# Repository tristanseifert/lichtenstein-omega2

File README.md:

# Lichtenstein Omega2+
This is a version of the Lichtenstein hardware, using an [Onion Omega2+](https://onion.io/omega2/) and a MAX V CPLD to drive up to eight LED strips at once.

Connectivity is provided by the Omega2's Ethernet peripheral. The board itself runs a custom version of LEDE, with the lichtenstein client app running and providing lichtenstein services on the local subnet.

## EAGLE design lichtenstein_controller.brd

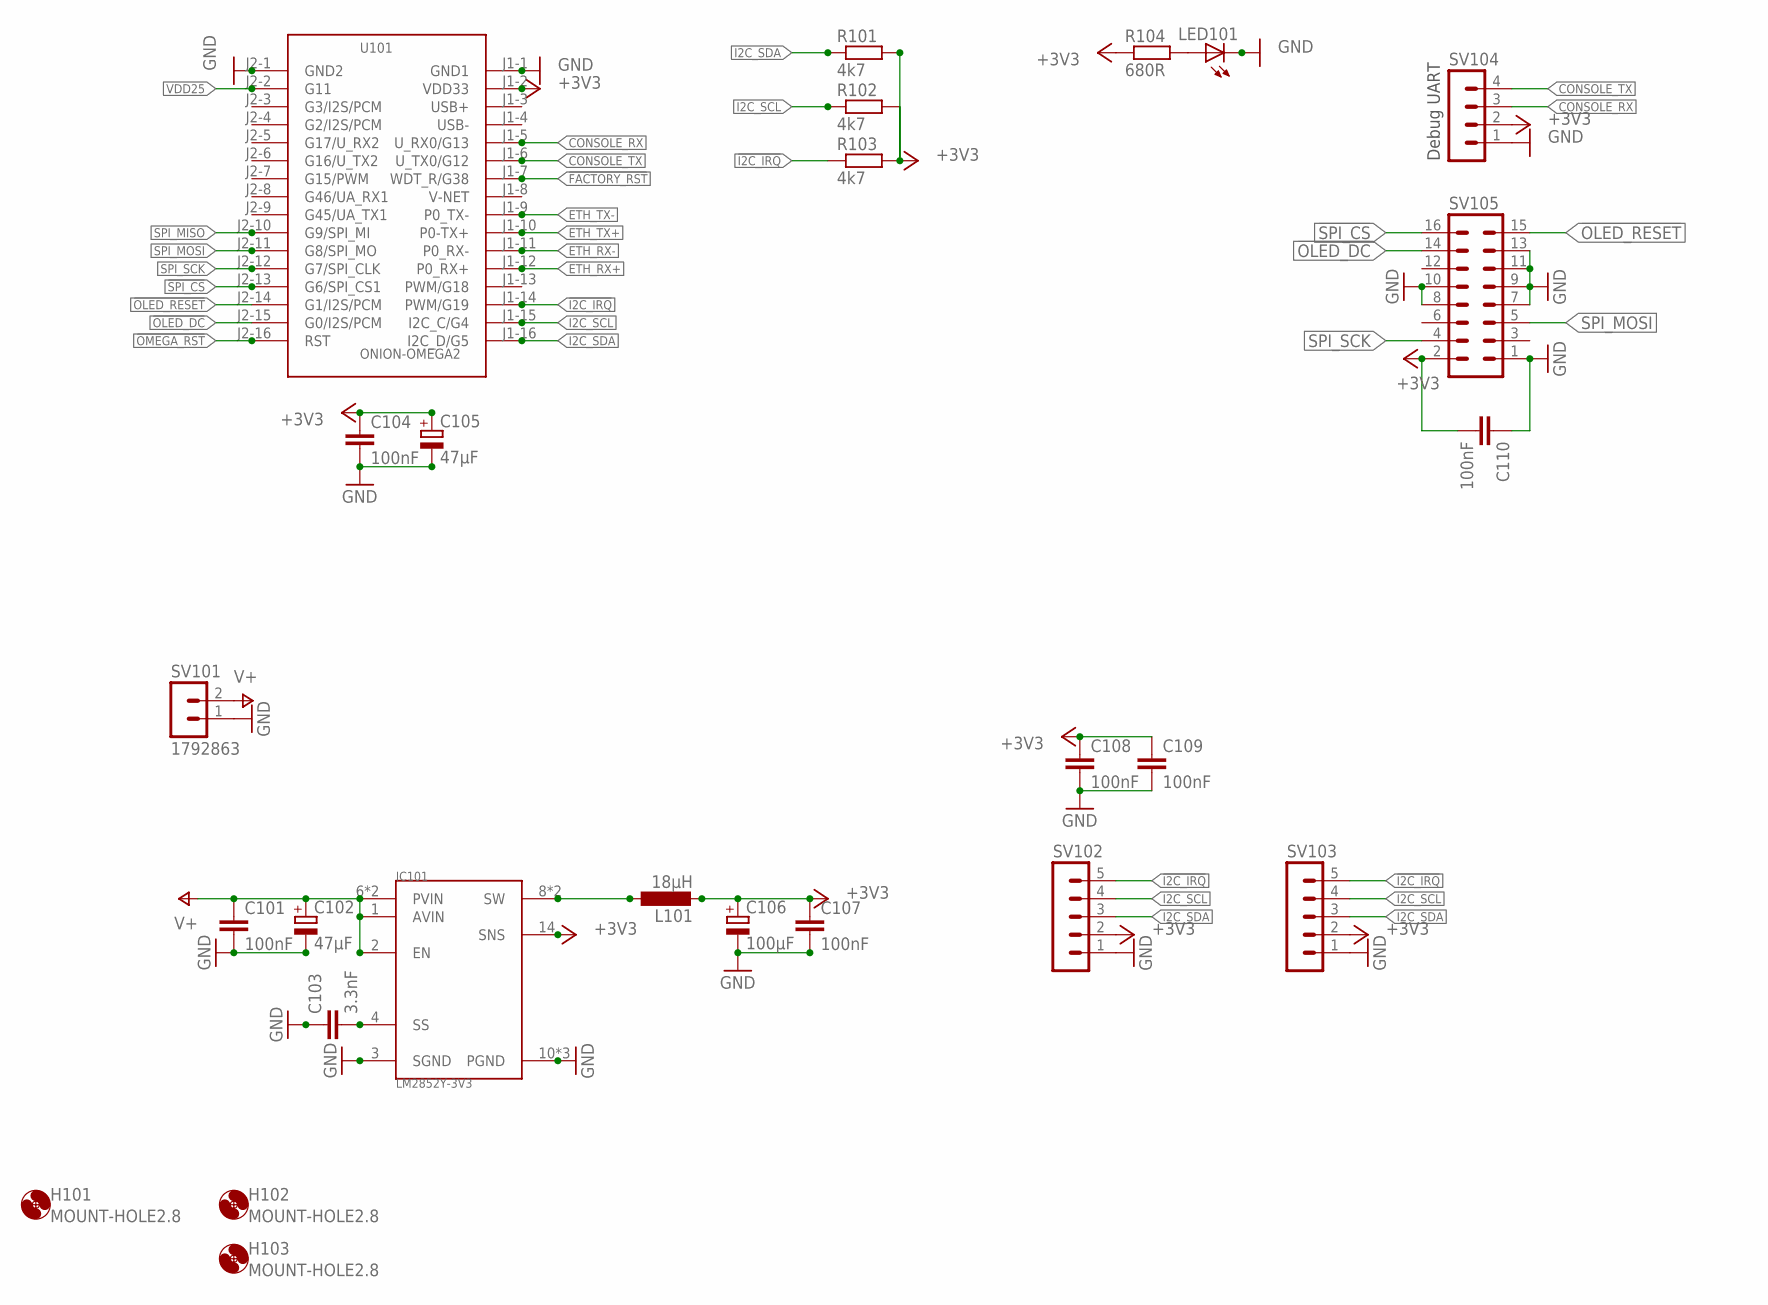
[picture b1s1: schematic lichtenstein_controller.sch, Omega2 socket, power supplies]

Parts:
C101, C104, C107, C108, C109, C110: 100nF; C0805; MOUSER 710-885012207072
C102, C105: 47µF; CT7343; MOUSER 581-TAJD476M016RNJV
C103: 3.3nF; C0805; MOUSER 710-885012207089
C106: 100µF; CT7343; MOUSER 581-NOSD107M006
H101, H102, H103: MOUNT-HOLE2.8; 2,8
IC101: LM2852Y-3V3; HTSSOP14
L101: 18µH; SRR1050A
LED101: LEDCHIPLED_1206; CHIPLED_1206; MOUSER 604-APTR3216SGC
R101, R102, R103: 4k7; M0805; MOUSER 652-CR0805-FX4701GLF
R104: 680R; M0805; MOUSER 652-CR0805-FX6800GLF
SV101: 1792863
SV102, SV103: MA05-1
SV104: MA04-1
SV105: MA08-2
U101: ONION-OMEGA2; ONION-2MM-2X16; MOUSER 353-OM-O2P

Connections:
!FACTORY_RST: U101.J1-7 (WDT_R/G38)
!I2C_IRQ: R103.1, SV102.5, SV103.5, U101.J1-14 (PWM/G19)
!OLED_DC: SV105.14, U101.J2-15 (G0/I2S/PCM)
!OLED_RESET: SV105.15, U101.J2-14 (G1/I2S/PCM)
!OMEGA_RST: U101.J2-16 (RST)
!SPI_CS: SV105.16, U101.J2-13 (G6/SPI_CS1)
+3V3: C104.1, C105.+, C106.+, C107.1, C108.1, C109.1, C110.2, IC101.14 (SNS), L101.P$2 (2), R101.2, R102.2, R103.2, R104.1, SV102.2, SV103.2, SV104.2, SV105.2, U101.J1-2 (VDD33)
CONSOLE_RX: SV104.3, U101.J1-5 (U_RX0/G13)
CONSOLE_TX: SV104.4, U101.J1-6 (U_TX0/G12)
ETH_RX+: U101.J1-12 (P0_RX+)
ETH_RX-: U101.J1-11 (P0_RX-)
ETH_TX+: U101.J1-10 (P0-TX+)
ETH_TX-: U101.J1-9 (P0_TX-)
GND: C101.2, C102.-, C103.1, C104.2, C105.-, C106.-, C107.2, C108.2, C109.2, C110.1, IC101.3 (SGND), IC101.10 (PGND), IC101.11 (PGND), IC101.PAD (PGND), LED101.C, SV101.1, SV102.1, SV103.1, SV104.1, SV105.1, SV105.7, SV105.8, SV105.9, SV105.10, SV105.11, SV105.13, U101.J1-1 (GND1), U101.J2-1 (GND2)
I2C_SCL: R102.1, SV102.4, SV103.4, U101.J1-15 (I2C_C/G4)
I2C_SDA: R101.1, SV102.3, SV103.3, U101.J1-16 (I2C_D/G5)
unnamed: LED101.A, R104.2
unnamed: IC101.8 (SW), IC101.9 (SW), L101.P$1 (1)
unnamed: C103.2, IC101.4 (SS)
SPI_MISO: U101.J2-10 (G9/SPI_MI)
SPI_MOSI: SV105.5, U101.J2-11 (G8/SPI_MO)
SPI_SCK: SV105.4, U101.J2-12 (G7/SPI_CLK)
V+: C101.1, C102.+, IC101.1 (AVIN), IC101.2 (EN), IC101.6 (PVIN), IC101.7 (PVIN), SV101.2
VDD25: U101.J2-2 (G11)

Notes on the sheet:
Debug UART

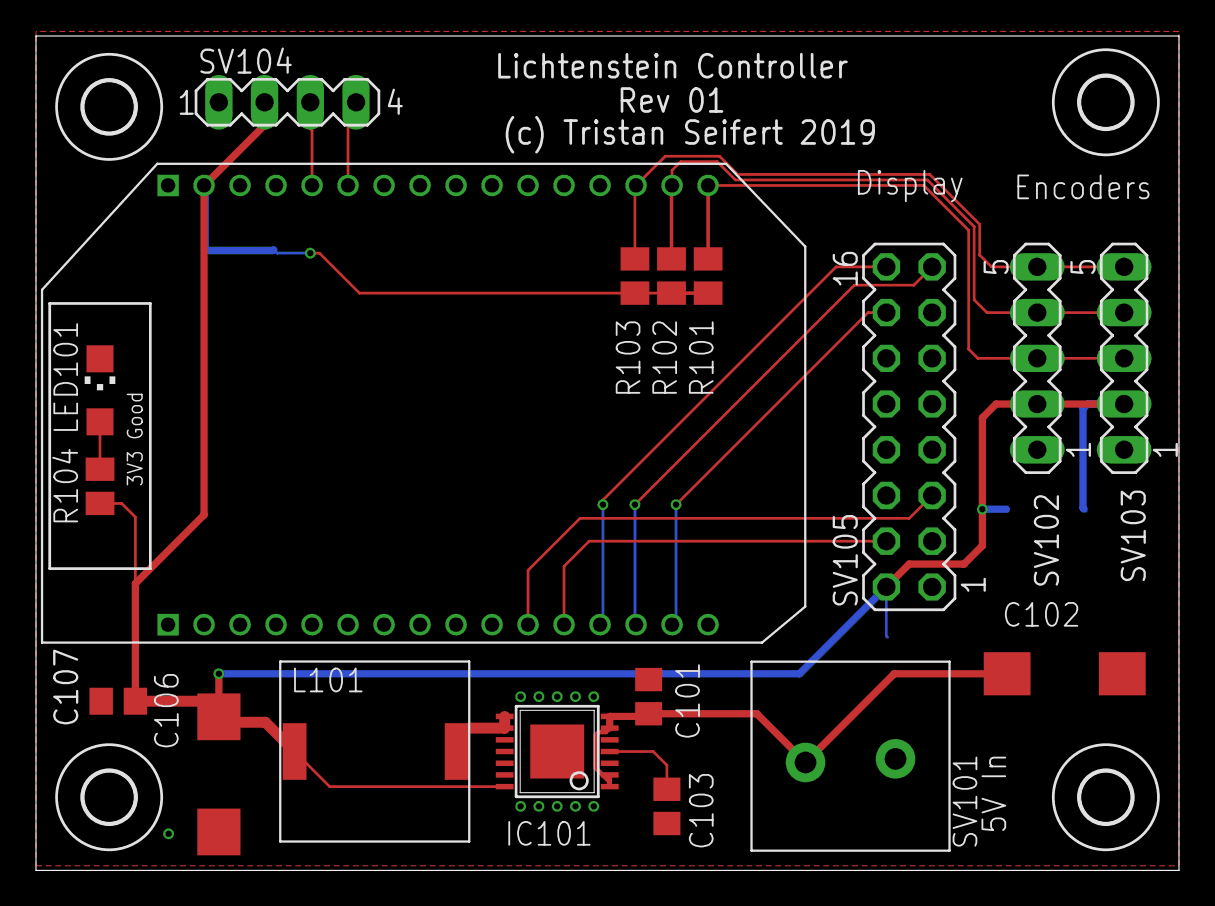
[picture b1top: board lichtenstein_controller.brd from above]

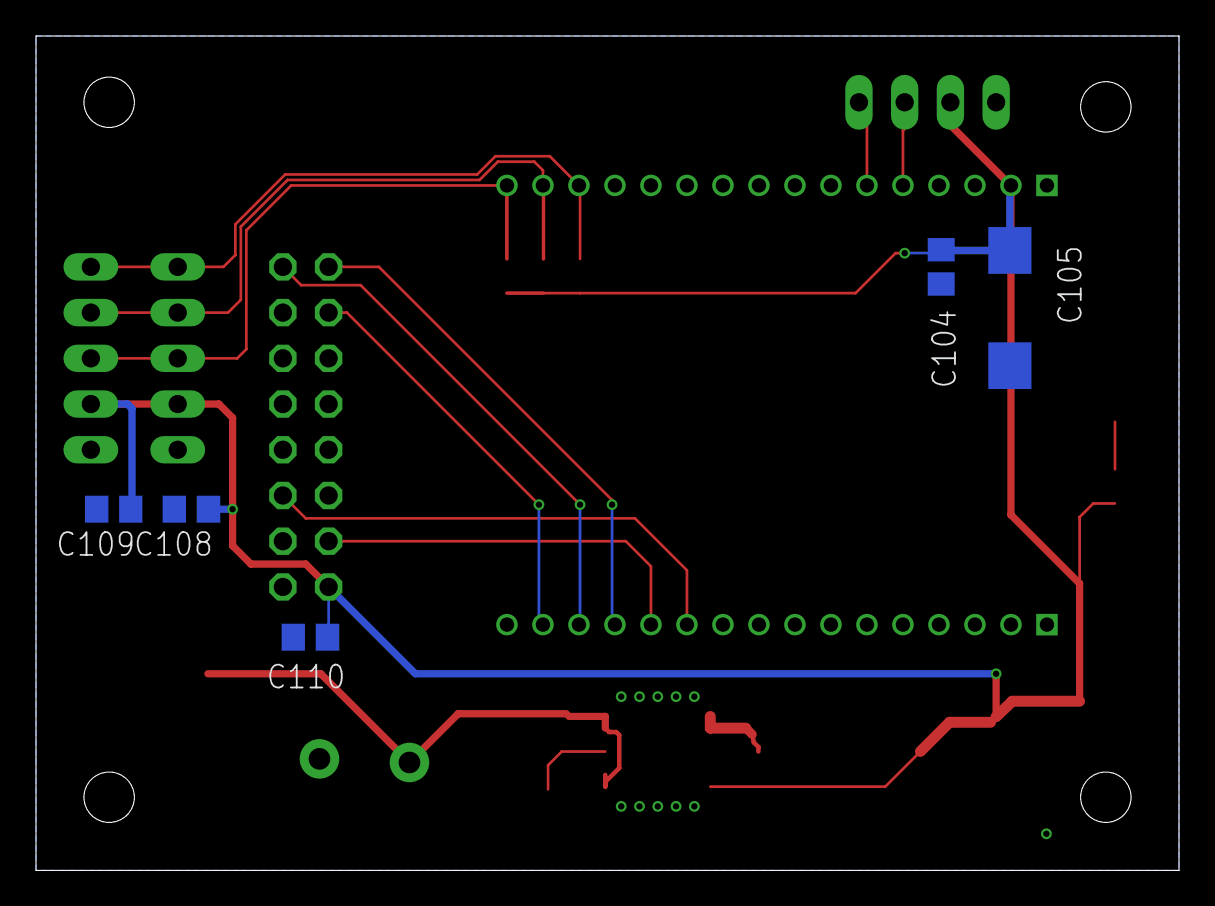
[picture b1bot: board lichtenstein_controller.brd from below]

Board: 2 copper layers, 63.5 x 46.4 mm, 27 parts (5 on the bottom side), 16 nets.

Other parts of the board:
H4: MOUNT-HOLE2.8; 2,8

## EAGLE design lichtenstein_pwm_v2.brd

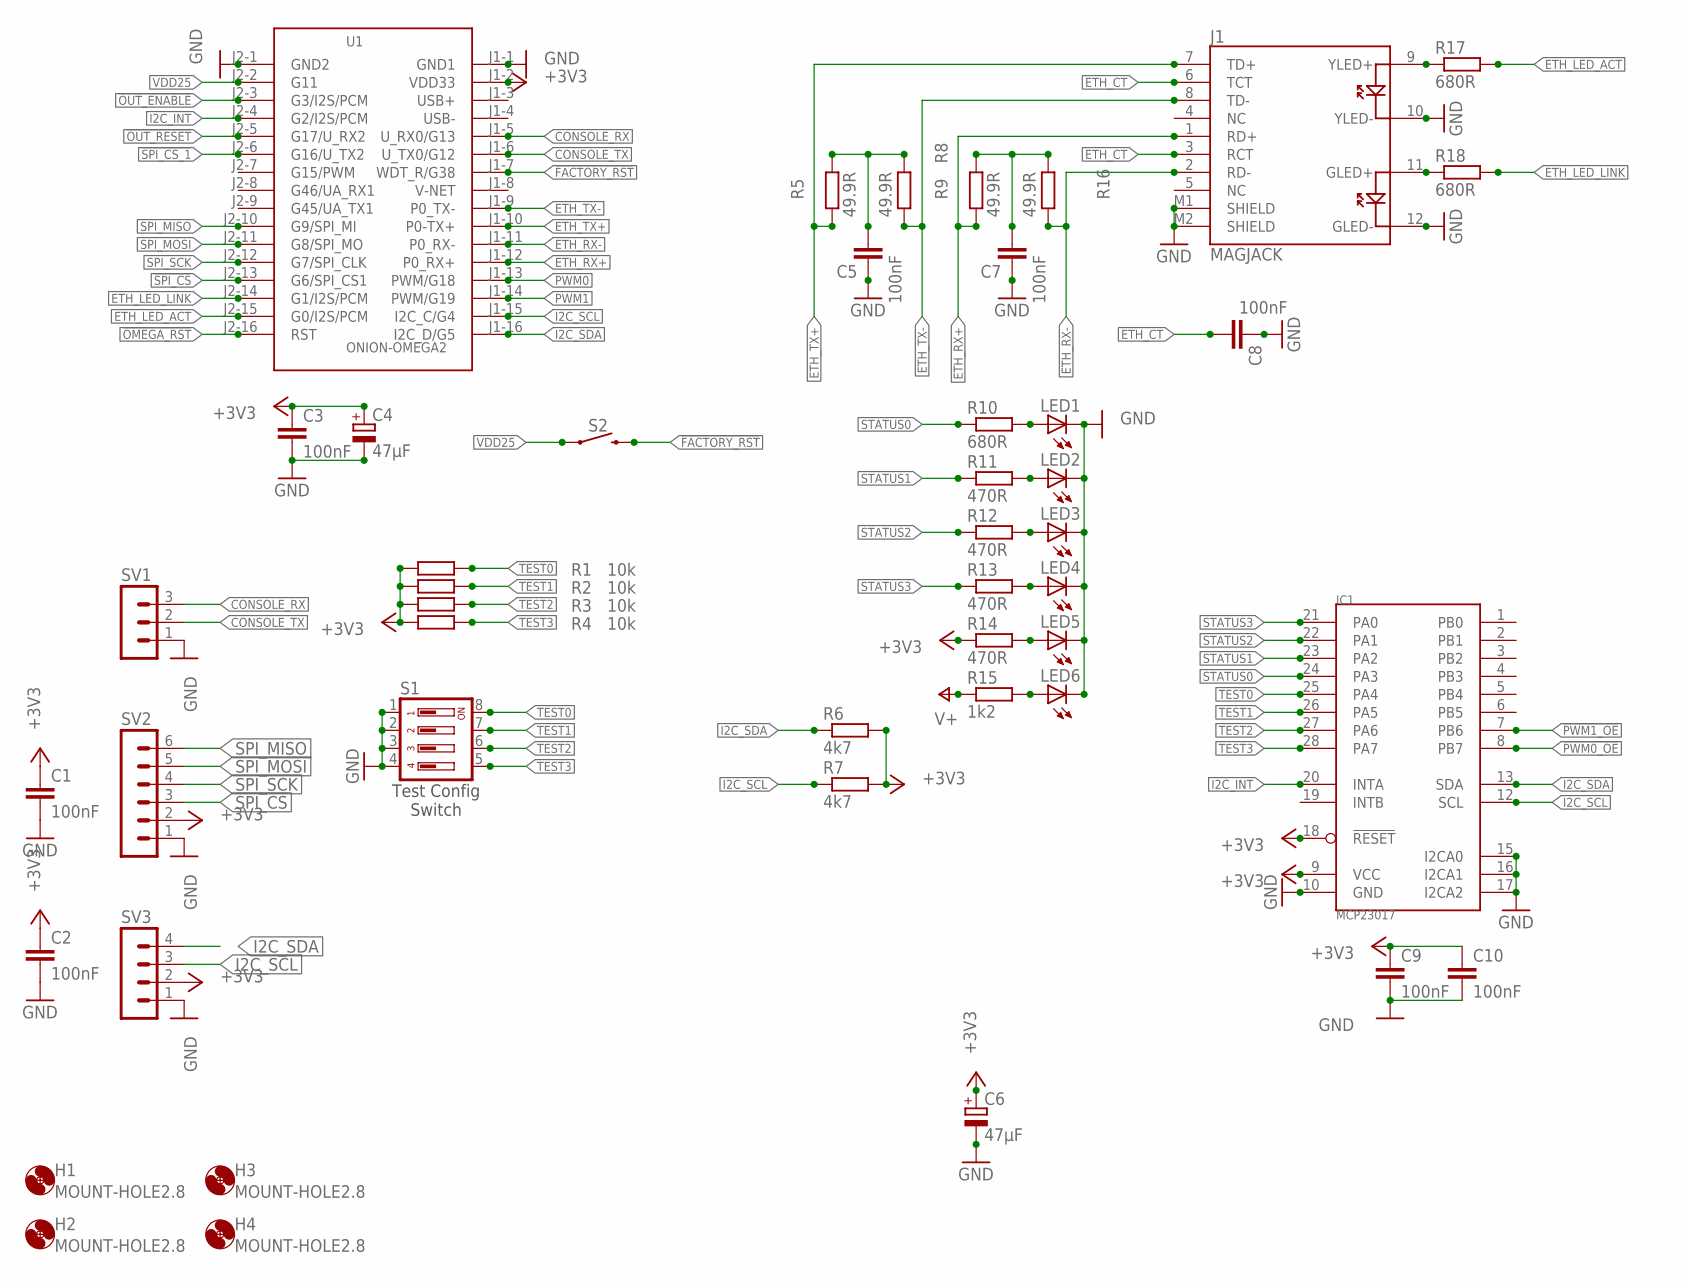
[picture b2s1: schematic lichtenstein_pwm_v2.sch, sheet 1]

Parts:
C1, C2, C3, C5, C7, C8, C9, C10: 100nF; C0805; MOUSER 710-885012207072
C4, C6: 47µF; SMC_C; MOUSER 581-TAJC476K016SNJ
H1, H2, H3, H4: MOUNT-HOLE2.8; 2,8
IC1: MCP23017; SO28W
J1: MAGJACK
LED1: LEDCHIPLED_1206; CHIPLED_1206; MOUSER 604-APTR3216SRCPRV
LED2, LED3, LED4, LED5, LED6: LEDCHIPLED_1206; CHIPLED_1206; MOUSER 604-APTR3216SGC
R1, R2, R3, R4: 10k; M0805; MOUSER 652-CR0805FX-1002ELF
R5, R9, R16: 49.9R; M0805; MOUSER 652-CR0805FX-49R9ELF
R6, R7: 4k7; M0805; MOUSER 652-CR0805-FX4701GLF
R8: 49.9R; M0805; MOUSER 652-CR0805-FX4701GLF
R10: 680R; M0805; MOUSER 667-ERJ-6ENF6800V
R11, R12, R13, R14: 470R; M0805; MOUSER 652-CR0805JW-471ELF
R15: 1k2; M0805; MOUSER 755-ESR10EZPJ122
R17, R18: 680R; M0805; MOUSER 652-CR0805-FX6800GLF
S1: 219-04; CTS-219-04; MOUSER 774-219-4LPS
S2: MOMENTARY-SWITCH-SPST-PTH-6.0MM; TACTILE_SWITCH_PTH_6.0MM; MOUSER 612-TL1105B
SV1: MA03-1
SV2: MA06-1
SV3: MA04-1
U1: ONION-OMEGA2; ONION-2MM-2X16; MOUSER 353-OM-O2P

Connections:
!FACTORY_RST: S2.3 (2), U1.J1-7 (WDT_R/G38)
!OMEGA_RST: U1.J2-16 (RST)
!OUT_ENABLE: U1.J2-3 (G3/I2S/PCM)
!OUT_RESET: U1.J2-5 (G17/U_RX2)
!PWM0_OE: IC1.8 (PB7); also elsewhere on the board
!PWM1_OE: IC1.7 (PB6); also elsewhere on the board
!SPI_CS: SV2.3, U1.J2-13 (G6/SPI_CS1)
!SPI_CS_1: U1.J2-6 (G16/U_TX2)
+3V3: C1.1, C2.1, C3.1, C4.+, C6.+, C9.1, C10.1, IC1.9 (VCC), IC1.18 (!RESET), R1.1, R2.1, R3.1, R4.1, R6.2, R7.2, R14.1, SV2.2, SV3.2, U1.J1-2 (VDD33); also elsewhere on the board
CONSOLE_RX: SV1.3, U1.J1-5 (U_RX0/G13)
CONSOLE_TX: SV1.2, U1.J1-6 (U_TX0/G12)
ETH_CT: C8.2, J1.3 (RCT), J1.6 (TCT)
ETH_LED_ACT: R17.2, U1.J2-15 (G0/I2S/PCM)
ETH_LED_LINK: R18.2, U1.J2-14 (G1/I2S/PCM)
ETH_RX+: J1.1 (RD+), R9.1, U1.J1-12 (P0_RX+)
ETH_RX-: J1.2 (RD-), R16.1, U1.J1-11 (P0_RX-)
ETH_TX+: J1.7 (TD+), R5.1, U1.J1-10 (P0-TX+)
ETH_TX-: J1.8 (TD-), R8.1, U1.J1-9 (P0_TX-)
GND: C1.2, C2.2, C3.2, C4.-, C5.1, C6.-, C7.1, C8.1, C9.2, C10.2, IC1.10 (GND), IC1.15 (I2CA0), IC1.16 (I2CA1), IC1.17 (I2CA2), J1.10 (YLED-), J1.12 (GLED-), J1.M1 (SHIELD), J1.M2 (SHIELD), LED1.C, LED2.C, LED3.C, LED4.C, LED5.C, LED6.C, S1.1, S1.2, S1.3, S1.4, SV1.1, SV2.1, SV3.1, U1.J1-1 (GND1), U1.J2-1 (GND2); also elsewhere on the board
I2C_INT: IC1.20 (INTA), U1.J2-4 (G2/I2S/PCM)
I2C_SCL: IC1.12 (SCL), R7.1, SV3.3, U1.J1-15 (I2C_C/G4); also elsewhere on the board
I2C_SDA: IC1.13 (SDA), R6.1, SV3.4, U1.J1-16 (I2C_D/G5); also elsewhere on the board
unnamed: LED5.A, R14.2
unnamed: LED1.A, R10.2
unnamed: C5.2, R5.2, R8.2
unnamed: J1.9 (YLED+), R17.1
unnamed: J1.11 (GLED+), R18.1
unnamed: C7.2, R9.2, R16.2
unnamed: LED2.A, R11.2
unnamed: LED3.A, R12.2
unnamed: LED4.A, R13.2
unnamed: LED6.A, R15.2
PWM0: U1.J1-13 (PWM/G18); also elsewhere on the board
PWM1: U1.J1-14 (PWM/G19); also elsewhere on the board
SPI_MISO: SV2.6, U1.J2-10 (G9/SPI_MI)
SPI_MOSI: SV2.5, U1.J2-11 (G8/SPI_MO)
SPI_SCK: SV2.4, U1.J2-12 (G7/SPI_CLK)
STATUS0: IC1.24 (PA3), R10.1
STATUS1: IC1.23 (PA2), R11.1
STATUS2: IC1.22 (PA1), R12.1
STATUS3: IC1.21 (PA0), R13.1
TEST0: IC1.25 (PA4), R1.2, S1.8
TEST1: IC1.26 (PA5), R2.2, S1.7
TEST2: IC1.27 (PA6), R3.2, S1.6
TEST3: IC1.28 (PA7), R4.2, S1.5
V+: R15.1; also elsewhere on the board
VDD25: S2.1, U1.J2-2 (G11)

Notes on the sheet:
Test Config Switch

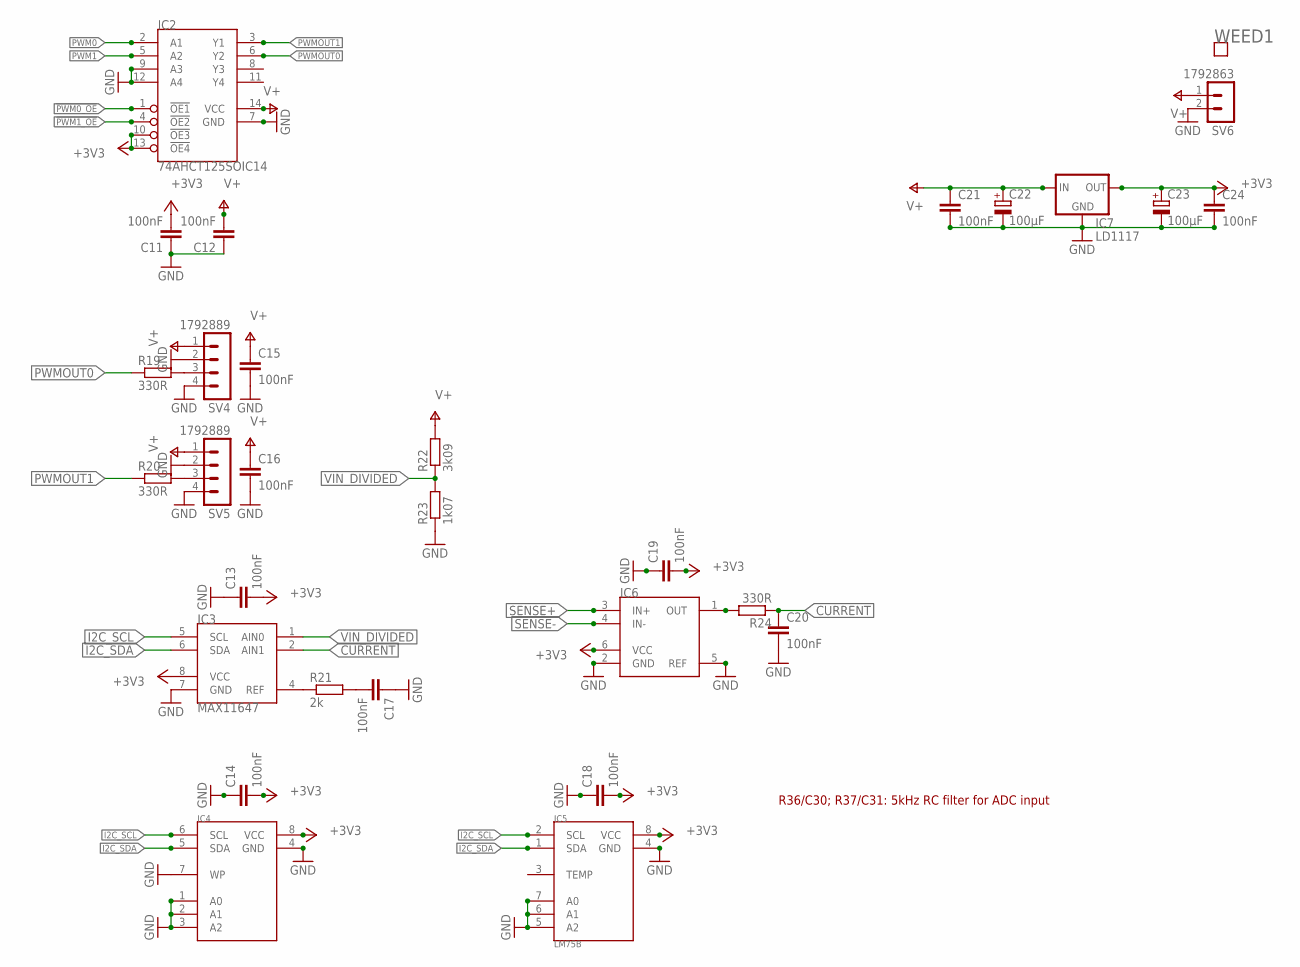
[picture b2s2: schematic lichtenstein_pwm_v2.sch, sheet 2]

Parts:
C11, C12, C13, C14, C15, C16, C17, C18, C19, C20, C21, C24: 100nF; C0805; MOUSER 710-885012207072
C22: 100µF; PANASONIC_D; MOUSER 667-EEE-HC1C101XP
C23: 100µF; CT7343; MOUSER 581-NOSD107M006
IC2: 74AHCT125SOIC14; SO14
IC3: MAX11647; UMAX8
IC4: AT24C02DSOIC-8; SOIC8
IC5: LM75B; SOIC8
IC6: INA18120VVSOT-23; SOT23-6L
IC7: LD1117; TO220V; MOUSER 490-VXO7803-500
R19, R20, R24: 330R; M0805; MOUSER 71-CRCW0805330RFKEAC
R21: 2k; M0805; MOUSER 667-ERJ-6ENF2001V
R22: 3k09; M0805; MOUSER 652-CR0805FX-3091ELF
R23: 1k07; M0805; MOUSER 652-CR0805FX-1071ELF
SV4, SV5: 1792889
SV6: 1792863
WEED1: WEED; DOINK

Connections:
!PWM0_OE: IC2.1 (!OE1); also elsewhere on the board
!PWM1_OE: IC2.4 (!OE2); also elsewhere on the board
+3V3: C11.2, C13.2, C14.2, C18.2, C19.2, C23.+, C24.1, IC2.10 (!OE3), IC2.13 (!OE4), IC3.8 (VCC), IC4.8 (VCC), IC5.8 (VCC), IC6.6 (VCC), IC7.2 (OUT); also elsewhere on the board
CURRENT: C20.1, IC3.2 (AIN1), R24.1
GND: C11.1, C12.1, C13.1, C14.1, C15.2, C16.2, C17.1, C18.1, C19.1, C20.2, C21.2, C22.-, C23.-, C24.2, IC2.7 (GND), IC2.9 (A3), IC2.12 (A4), IC3.7 (GND), IC4.1 (A0), IC4.2 (A1), IC4.3 (A2), IC4.4 (GND), IC4.7 (WP), IC5.4 (GND), IC5.5 (A2), IC5.6 (A1), IC5.7 (A0), IC6.2 (GND), IC6.5 (REF), IC7.1 (GND), R23.1, SV4.2, SV4.4, SV5.2, SV5.4, SV6.2; also elsewhere on the board
I2C_SCL: IC3.5 (SCL), IC4.6 (SCL), IC5.2 (SCL); also elsewhere on the board
I2C_SDA: IC3.6 (SDA), IC4.5 (SDA), IC5.1 (SDA); also elsewhere on the board
unnamed: R19.2, SV4.3
unnamed: R20.2, SV5.3
unnamed: IC3.4 (REF), R21.1
unnamed: C17.2, R21.2
unnamed: IC6.1 (OUT), R24.2
PWM0: IC2.2 (A1); also elsewhere on the board
PWM1: IC2.5 (A2); also elsewhere on the board
PWMOUT0: IC2.6 (Y2), R19.1
PWMOUT1: IC2.3 (Y1), R20.1
SENSE+: IC6.3 (IN+)
SENSE-: IC6.4 (IN-)
V+: C12.2, C15.1, C16.1, C21.1, C22.+, IC2.14 (VCC), IC7.3 (IN), R22.2, SV4.1, SV5.1, SV6.1; also elsewhere on the board
VIN_DIVIDED: IC3.1 (AIN0), R22.1, R23.2

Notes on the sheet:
R36/C30; R37/C31: 5kHz RC filter for ADC input

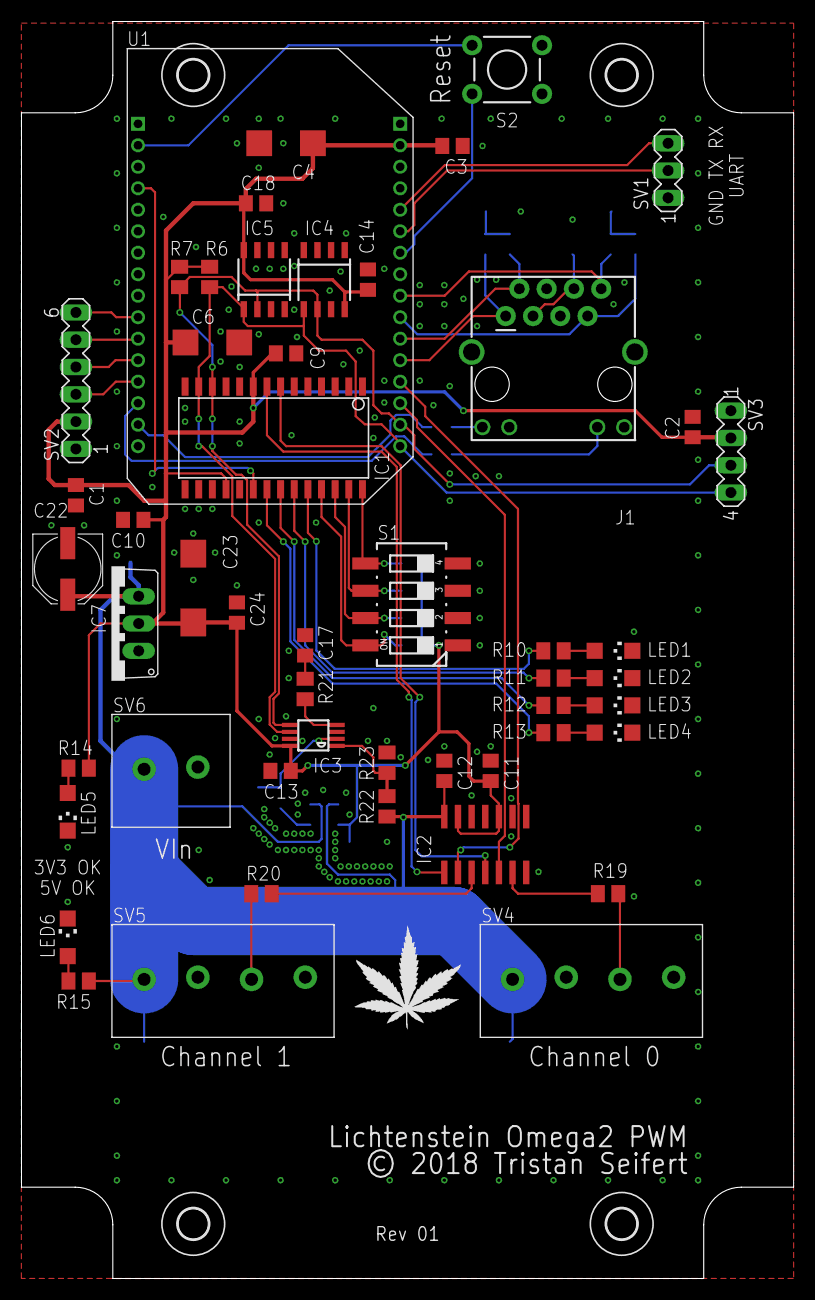
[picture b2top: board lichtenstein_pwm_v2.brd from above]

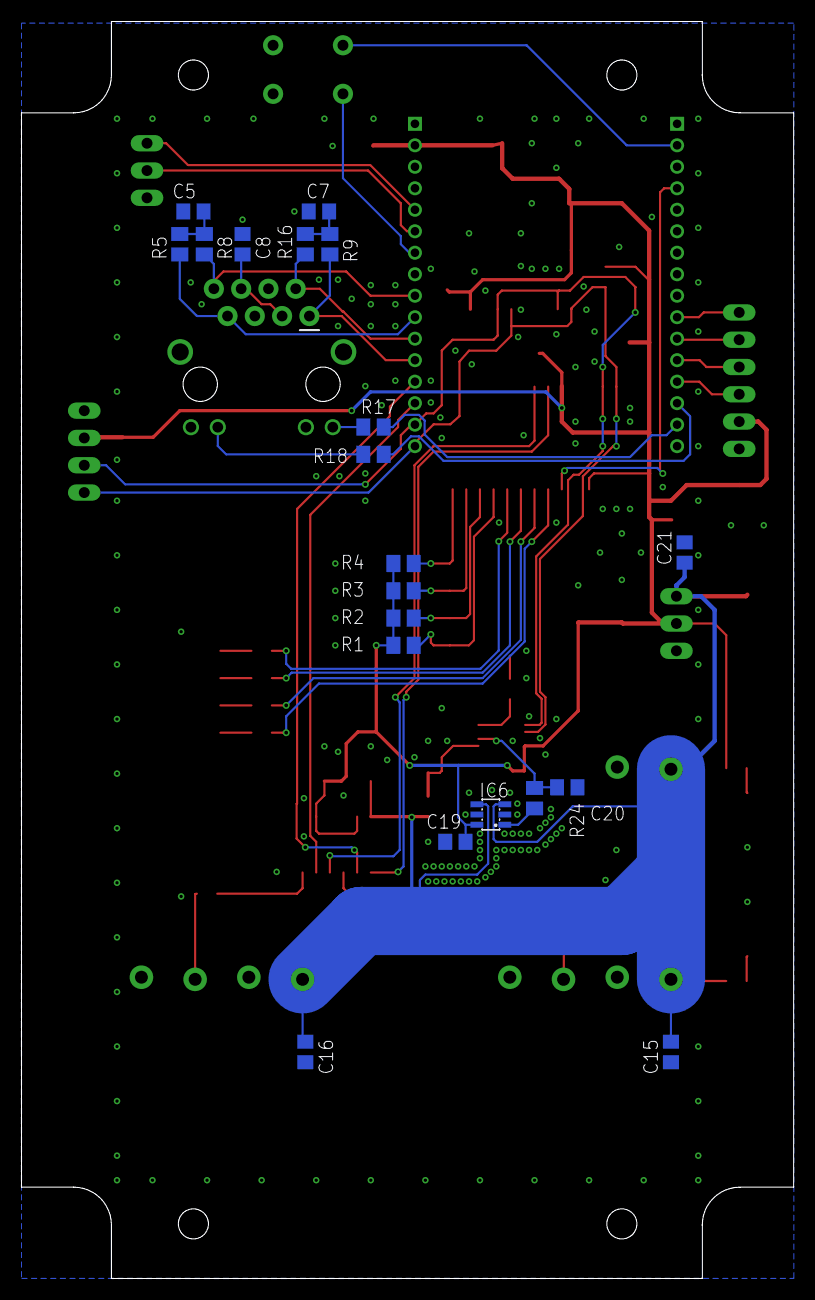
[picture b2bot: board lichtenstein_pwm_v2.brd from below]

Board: 2 copper layers, 71.9 x 117.0 mm, 76 parts (20 on the bottom side), 52 nets.

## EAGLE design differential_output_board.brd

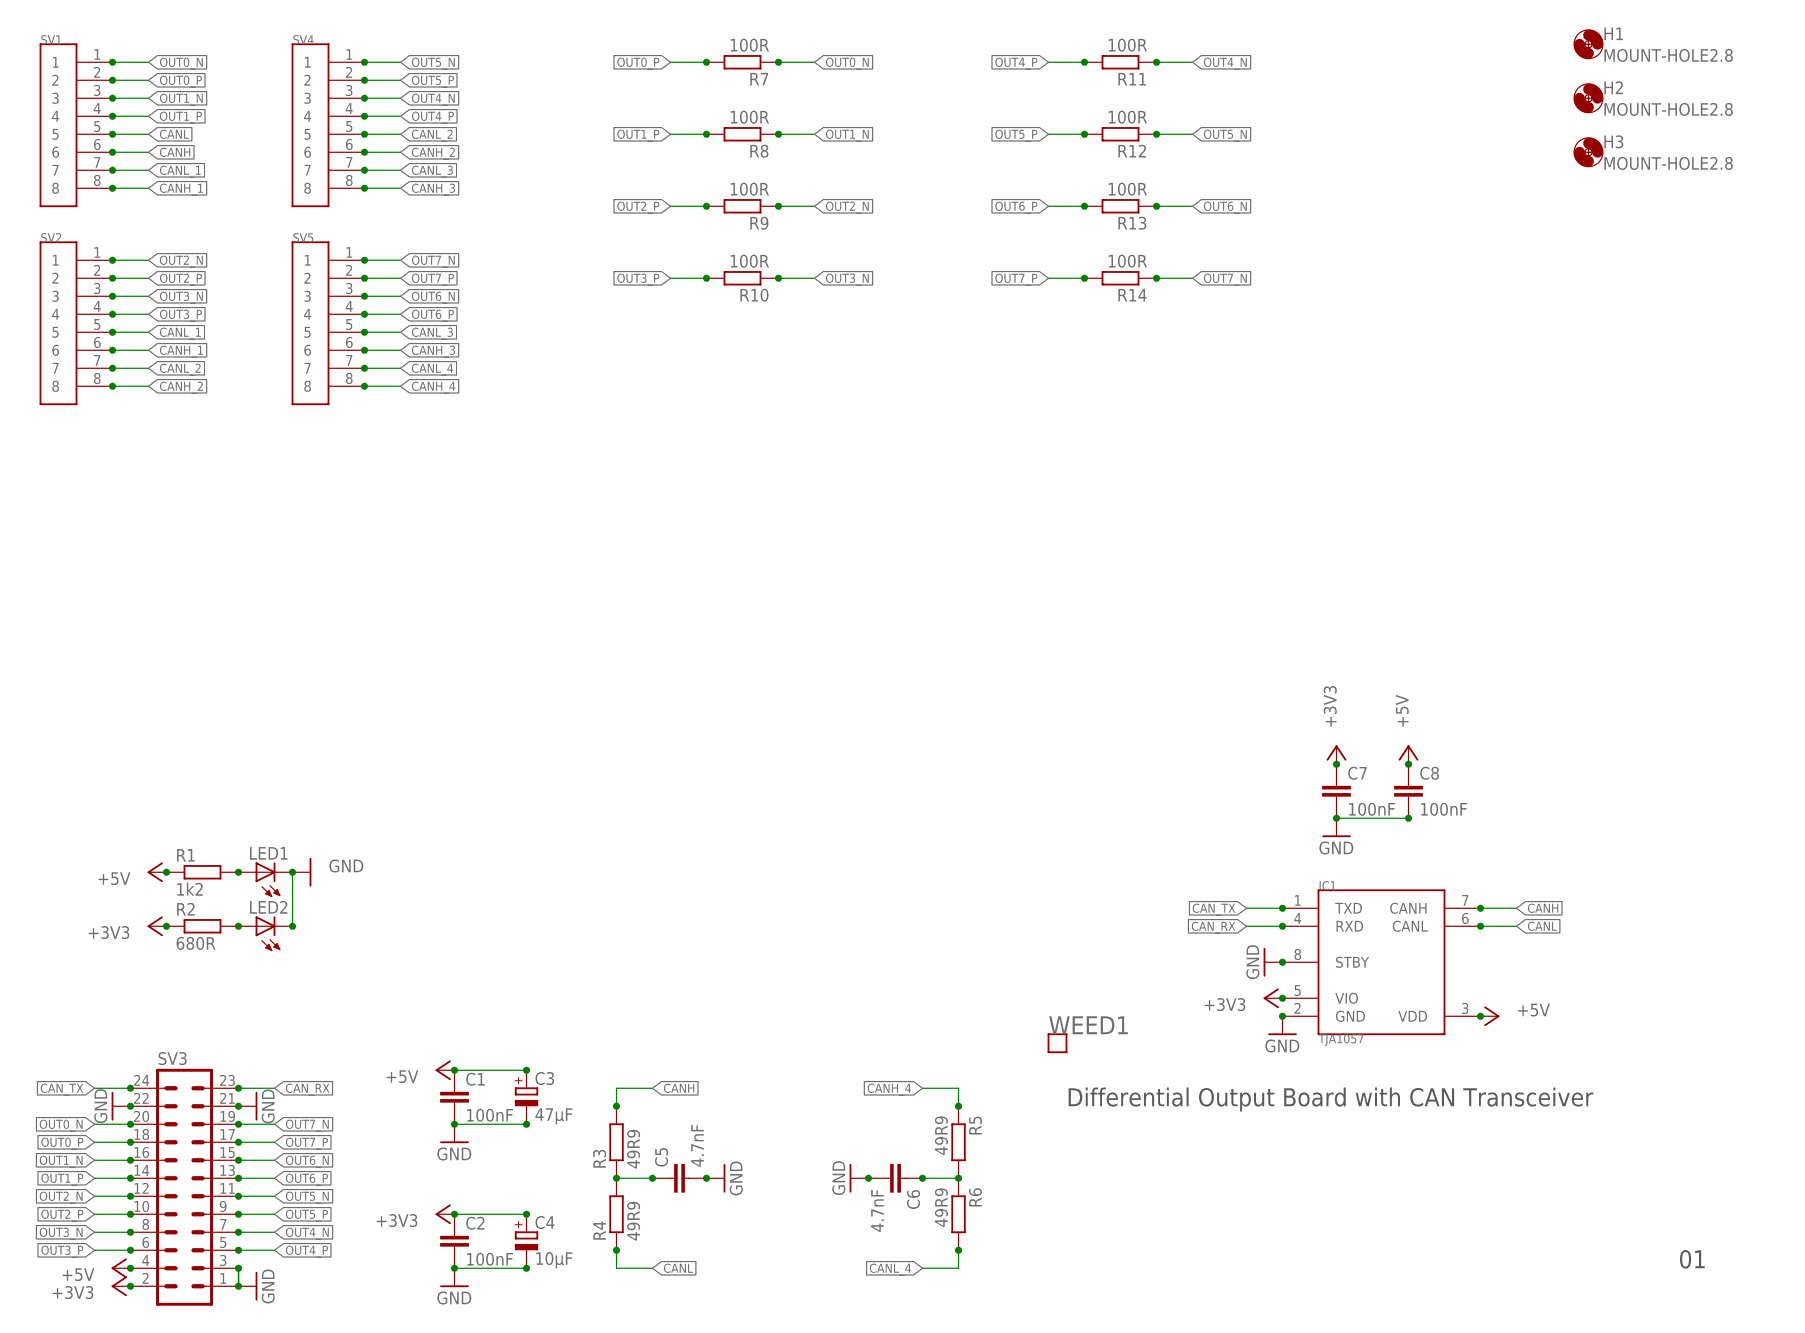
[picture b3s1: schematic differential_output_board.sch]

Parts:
C1, C2, C7, C8: 100nF; C0805; MOUSER 710-885012207072
C3: 47µF; SMC_D; MOUSER 581-TAJD476M016RNJV
C4: 10µF; SMC_B; MOUSER 581-TAJB106K020RNJV
C5, C6: 4.7nF; C0805; MOUSER 710-885012207037
H1, H2, H3: MOUNT-HOLE2.8; 2,8
IC1: TJA1057; SOIC8
LED1, LED2: LEDCHIPLED_1206; CHIPLED_1206; MOUSER 604-APTR3216SGC
R1: 1k2; M0805; MOUSER 652-CR0805FX-1201ELF
R2: 680R; M0805; MOUSER 652-CR0805-FX6800GLF
R3, R4, R5, R6: 49R9; M1206; MOUSER 71-CRCW120649R9FKEAC
R7, R8, R9, R10, R11, R12, R13, R14: 100R; M1206; MOUSER 652-CR1206FX-1000ELF
SV1, SV2, SV4, SV5: SS-51000-003
SV3: MA12-2; MOUSER 517-30320-6002
WEED1: WEED; DOINK

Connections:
+3V3: C2.1, C4.+, C7.1, IC1.5 (VIO), R2.1, SV3.2
+5V: C1.1, C3.+, C8.1, IC1.3 (VDD), R1.1, SV3.4
CANH: IC1.7 (CANH), R3.2, SV1.6
CANH_1: SV1.8, SV2.6
CANH_2: SV2.8, SV4.6
CANH_3: SV4.8, SV5.6
CANH_4: R5.1, SV5.8
CANL: IC1.6 (CANL), R4.1, SV1.5
CANL_1: SV1.7, SV2.5
CANL_2: SV2.7, SV4.5
CANL_3: SV4.7, SV5.5
CANL_4: R6.2, SV5.7
CAN_RX: IC1.4 (RXD), SV3.23
CAN_TX: IC1.1 (TXD), SV3.24
GND: C1.2, C2.2, C3.-, C4.-, C5.2, C6.2, C7.2, C8.2, IC1.2 (GND), IC1.8 (STBY), LED1.C, LED2.C, SV3.1, SV3.3, SV3.21, SV3.22
unnamed: C5.1, R3.1, R4.2
unnamed: C6.1, R5.2, R6.1
unnamed: LED1.A, R1.2
unnamed: LED2.A, R2.2
OUT0_N: R7.1, SV1.1, SV3.20
OUT0_P: R7.2, SV1.2, SV3.18
OUT1_N: R8.1, SV1.3, SV3.16
OUT1_P: R8.2, SV1.4, SV3.14
OUT2_N: R9.1, SV2.1, SV3.12
OUT2_P: R9.2, SV2.2, SV3.10
OUT3_N: R10.1, SV2.3, SV3.8
OUT3_P: R10.2, SV2.4, SV3.6
OUT4_N: R11.1, SV3.7, SV4.3
OUT4_P: R11.2, SV3.5, SV4.4
OUT5_N: R12.1, SV3.11, SV4.1
OUT5_P: R12.2, SV3.9, SV4.2
OUT6_N: R13.1, SV3.15, SV5.3
OUT6_P: R13.2, SV3.13, SV5.4
OUT7_N: R14.1, SV3.19, SV5.1
OUT7_P: R14.2, SV3.17, SV5.2

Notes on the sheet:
Differential Output Board with CAN Transceiver

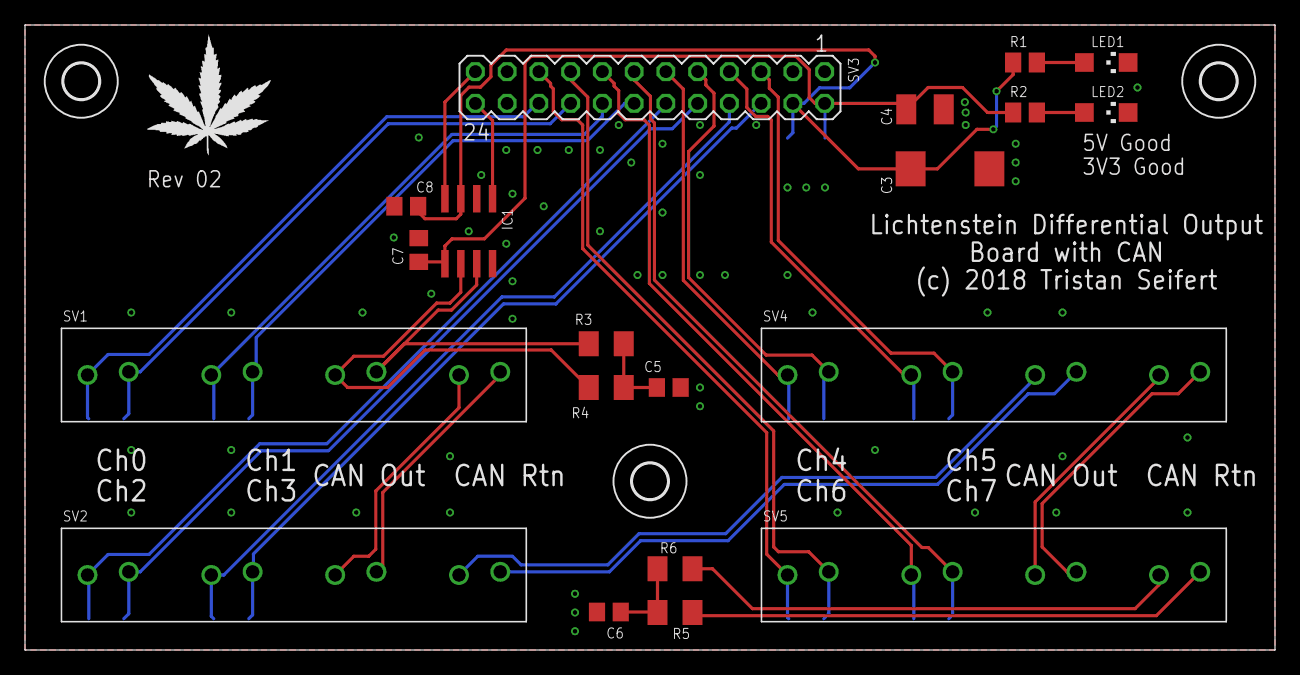
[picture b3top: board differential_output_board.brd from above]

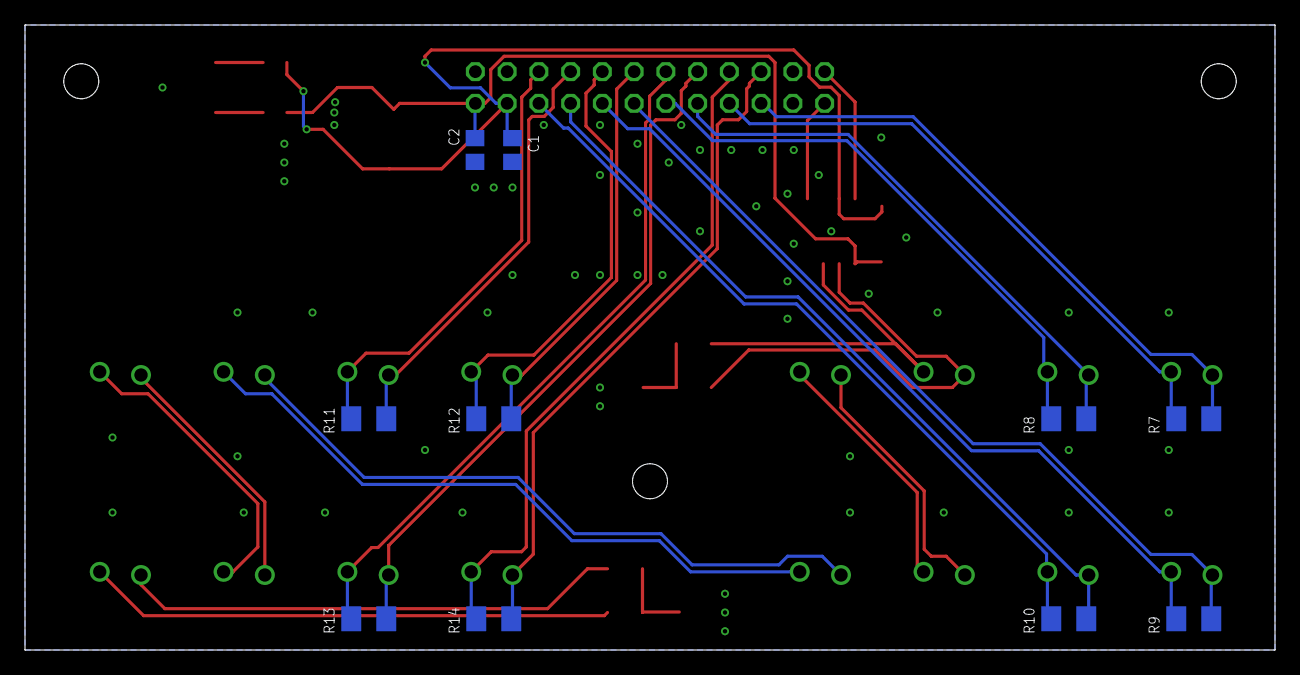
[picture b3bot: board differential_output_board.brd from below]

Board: 2 copper layers, 100.0 x 50.0 mm, 34 parts (10 on the bottom side), 35 nets.

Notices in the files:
differential_led_board.brd:
© 2018 Tristan Seifert
differential_output_board.brd:
(c) 2018 Tristan Seifert
parts and their libraries:
SparkFun-Connectors: Licensing: Creative Commons ShareAlike 4.0 International - https://creativecommons.org/licenses/by-sa/4.0
